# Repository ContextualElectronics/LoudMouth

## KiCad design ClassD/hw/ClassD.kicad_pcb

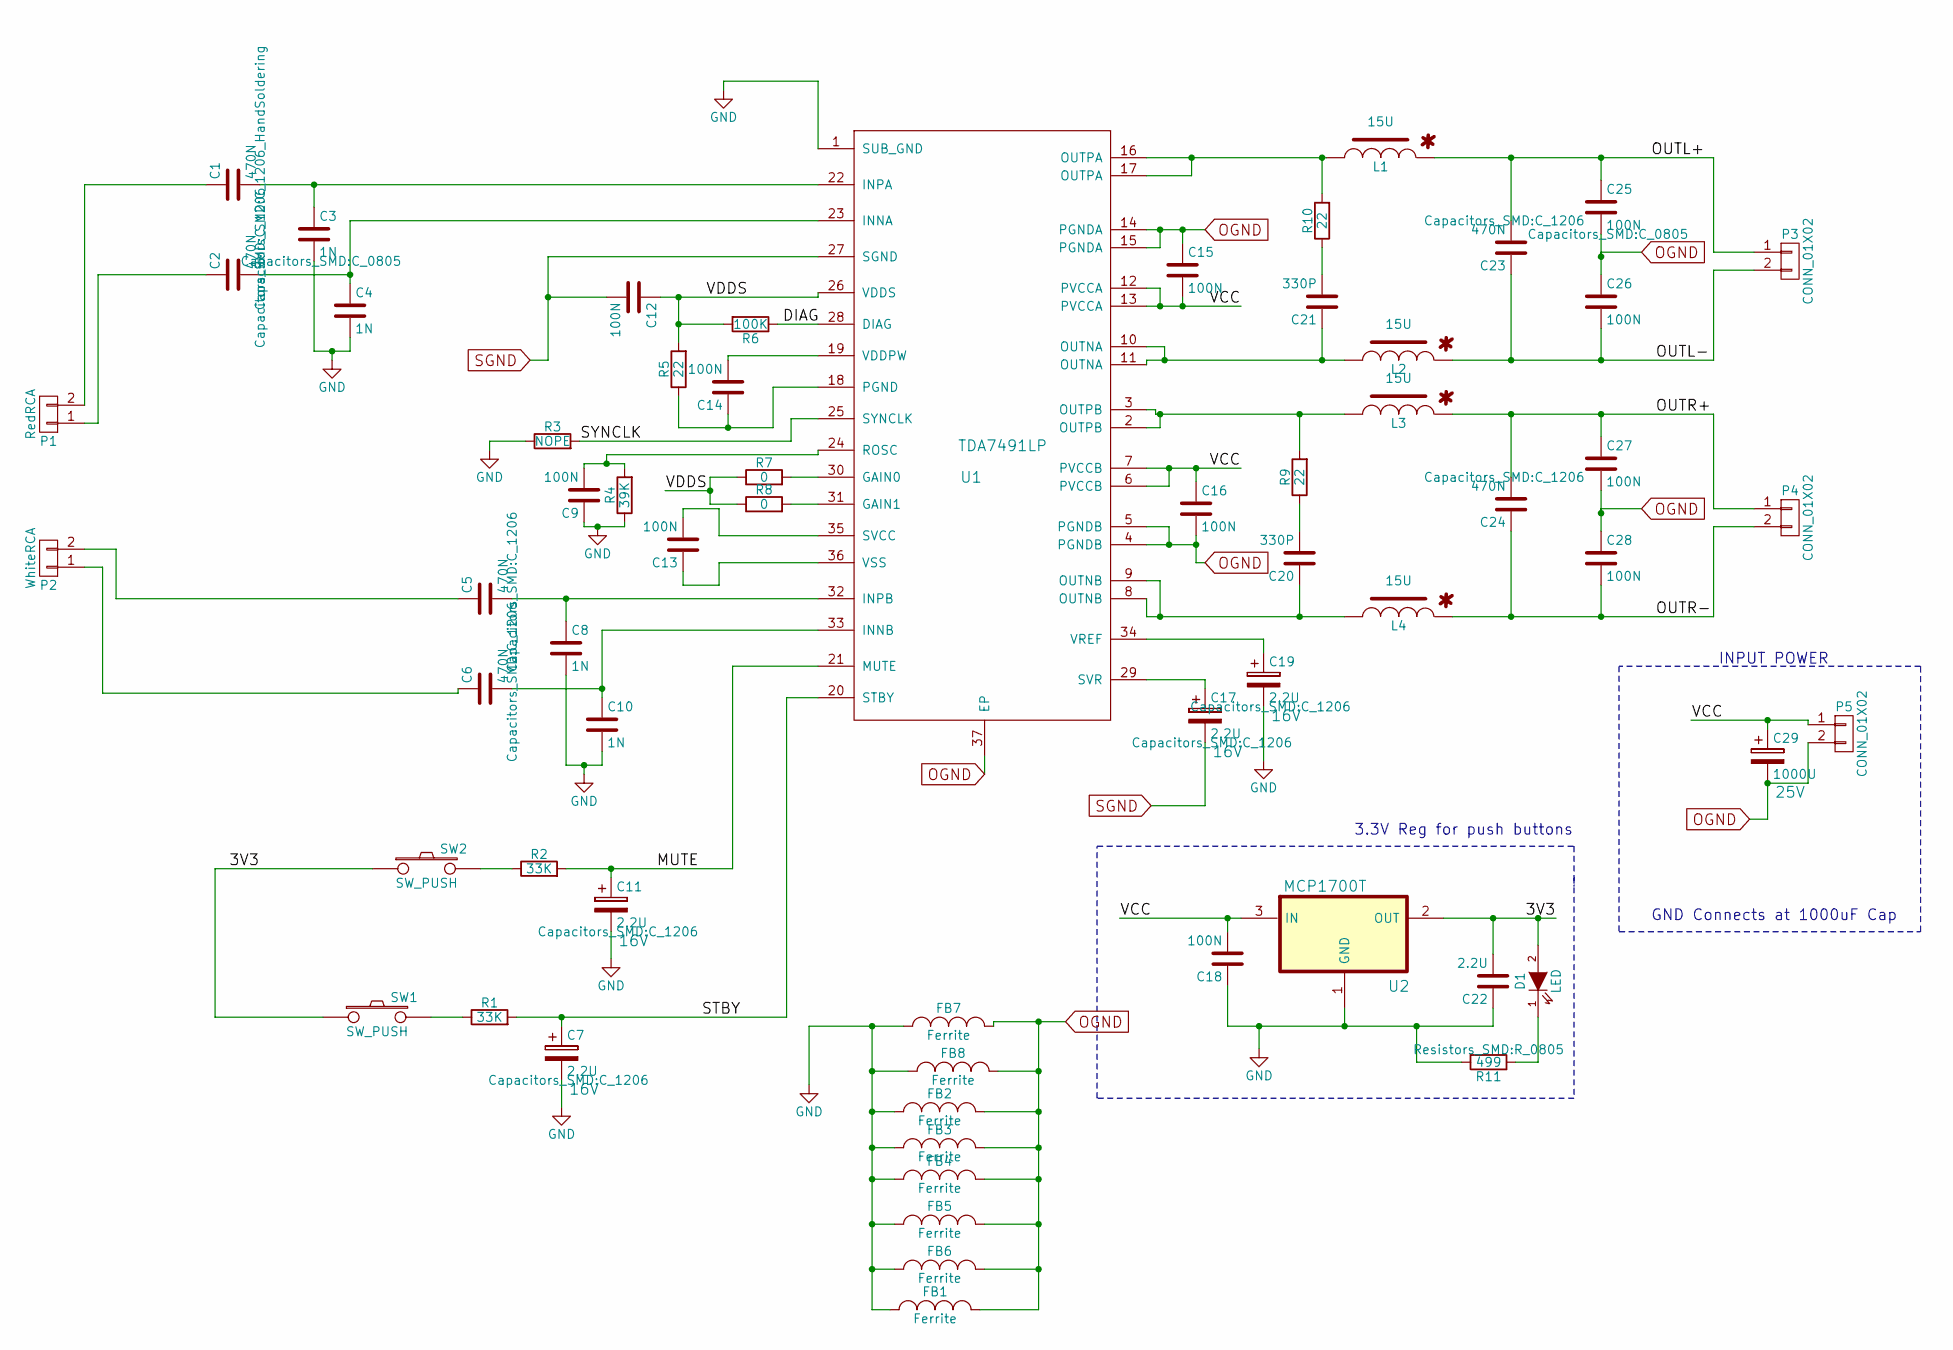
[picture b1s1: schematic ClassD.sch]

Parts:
C1: 470N; C_1206_HandSoldering; Voltage 25; MPN CL31B474KAFNNNE
C2, C5, C6, C23, C24: 470N; C_1206; Voltage 25; MPN CL31B474KAFNNNE
C3: 1N; C_0805; MPN C0805C102K5RACTU
C4, C8, C10: 1N; C_0805
C7, C11, C17, C19: 2.2U; C_1206; Voltage 16V; MPN C3216X7R1E225K160AA
C9, C12, C13, C14, C15, C16, C18, C26, C27, C28: 100N; C_0805
C20, C21: 330P; C_0805; MPN 0805YC334KAT2A
C22: 2.2U; C_1206
C25: 100N; C_0805; Voltage 16; MPN C0805C104K4RACTU
C29: 1000U; c_elec_13.6x13.6; Voltage 25V; MPN UUG1E102MNQ1MS
D1: LED; LED_0805
FB1, FB2, FB3, FB4, FB5, FB6, FB7, FB8: Ferrite; R_0805
L1, L2, L3, L4: 15U; NRS6045T150MMGK; MPN NRS6045T150MMGK
P1: RedRCA; RCJ1x; MPN RCJ-012
P2: WhiteRCA; RCJ1x; MPN RCJ013
P3, P4, P5: CONN_01X02; Pin_Header_Straight_1x02
R1, R2: 33K; R_0805
R3: NOPE; R_0805
R4: 39K; R_0805
R5, R9, R10: 22; R_0805
R6: 100K; R_0805
R7, R8: 0; R_0805
R11: 499; R_0805
SW1, SW2: SW_PUSH; FSM2JSMAA-ND; MPN FSM2JSMAA
U1: TDA7491LP; PowerSSO36-EPD; MPN TDA7491LP13TR
U2: MCP1700T; SOT-23; Voltage 3.3; MPN MCP1700T-3302E/TT

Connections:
/3V3: C22.2, D1.2 (A), SW1.1, SW2.1, U2.2 (OUT)
/DIAG: R6.1, U1.28 (DIAG)
/MUTE: C11.1, R2.2, U1.21 (MUTE)
/OUTL+: C23.2, C25.1, L1.1, P3.1
/OUTL-: C23.1, C26.2, L2.1, P3.2
/OUTR+: C24.2, C27.1, L3.1, P4.1
/OUTR-: C24.1, C28.2, L4.1, P4.2
/STBY: C7.1, R1.2, U1.20 (STBY)
/SYNCLK: R3.2, U1.25 (SYNCLK)
/VCC: C15.2, C16.1, C18.2, C29.1, P5.1, U1.6 (PVCCB), U1.7 (PVCCB), U1.12 (PVCCA), U1.13 (PVCCA), U2.3 (IN)
/VDDS: C12.1, R5.2, R6.2, R7.1, R8.1, U1.26 (VDDS)
GND: C3.2, C4.2, C7.2, C8.2, C9.1, C10.2, C11.2, C18.1, C19.2, C22.1, FB1.1, FB2.1, FB3.1, FB4.1, FB5.1, FB6.1, FB7.1, FB8.1, R3.1, R4.1, R11.2, U1.1 (SUB_GND), U2.1 (GND)
unnamed: C1.1, P1.2
unnamed: C1.2, C3.1, U1.22 (INPA)
unnamed: C2.1, P1.1
unnamed: C2.2, C4.1, U1.23 (INNA)
unnamed: C5.1, P2.2
unnamed: C5.2, C8.1, U1.32 (INPB)
unnamed: C6.1, P2.1
unnamed: C9.2, R4.2, U1.24 (ROSC)
unnamed: C6.2, C10.1, U1.33 (INNB)
unnamed: C13.1, U1.36 (VSS)
unnamed: C13.2, U1.35 (SVCC)
unnamed: C14.1, R5.1, U1.18 (PGND)
unnamed: C14.2, U1.19 (VDDPW)
unnamed: C17.1, U1.29 (SVR)
unnamed: C19.1, U1.34 (VREF)
unnamed: C20.1, L4.2, U1.8 (OUTNB), U1.9 (OUTNB)
unnamed: C20.2, R9.1
unnamed: C21.1, L2.2, U1.10 (OUTNA), U1.11 (OUTNA)
unnamed: C21.2, R10.1
unnamed: D1.1 (K), R11.1
unnamed: L1.2, R10.2, U1.16 (OUTPA), U1.17 (OUTPA)
unnamed: L3.2, R9.2, U1.2 (OUTPB), U1.3 (OUTPB)
unnamed: R1.1, SW1.2
unnamed: R2.1, SW2.2
unnamed: R7.2, U1.30 (GAIN0)
unnamed: R8.2, U1.31 (GAIN1)
OGND: C15.1, C16.2, C25.2, C26.1, C27.2, C28.1, C29.2, FB1.2, FB2.2, FB3.2, FB4.2, FB5.2, FB6.2, FB7.2, FB8.2, P5.2, U1.4 (PGNDB), U1.5 (PGNDB), U1.14 (PGNDA), U1.15 (PGNDA), U1.37 (EP)
SGND: C12.2, C17.2, U1.27 (SGND)

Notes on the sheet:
GND Connects at 1000uF Cap
INPUT POWER
3.3V Reg for push buttons

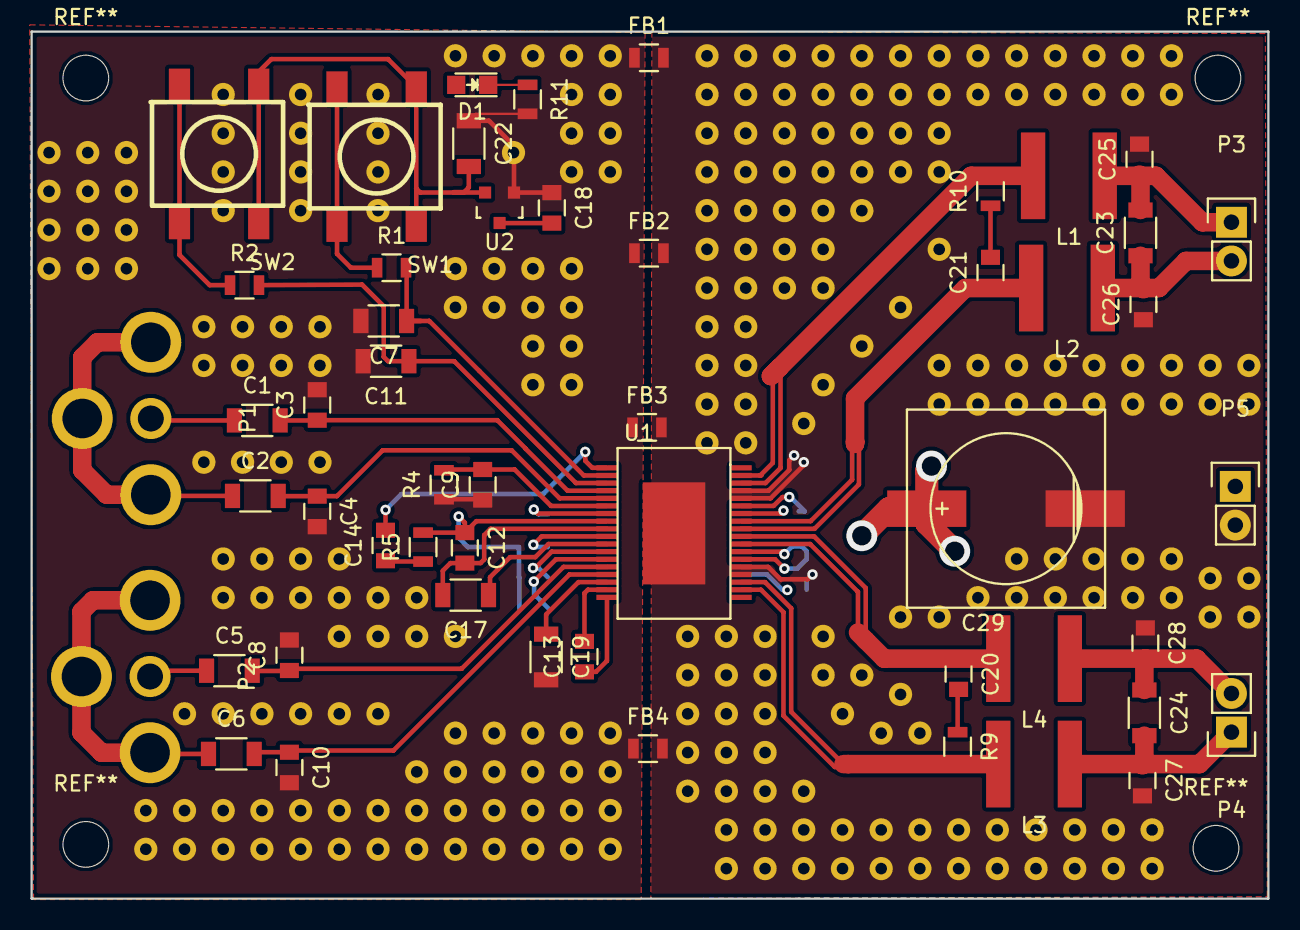
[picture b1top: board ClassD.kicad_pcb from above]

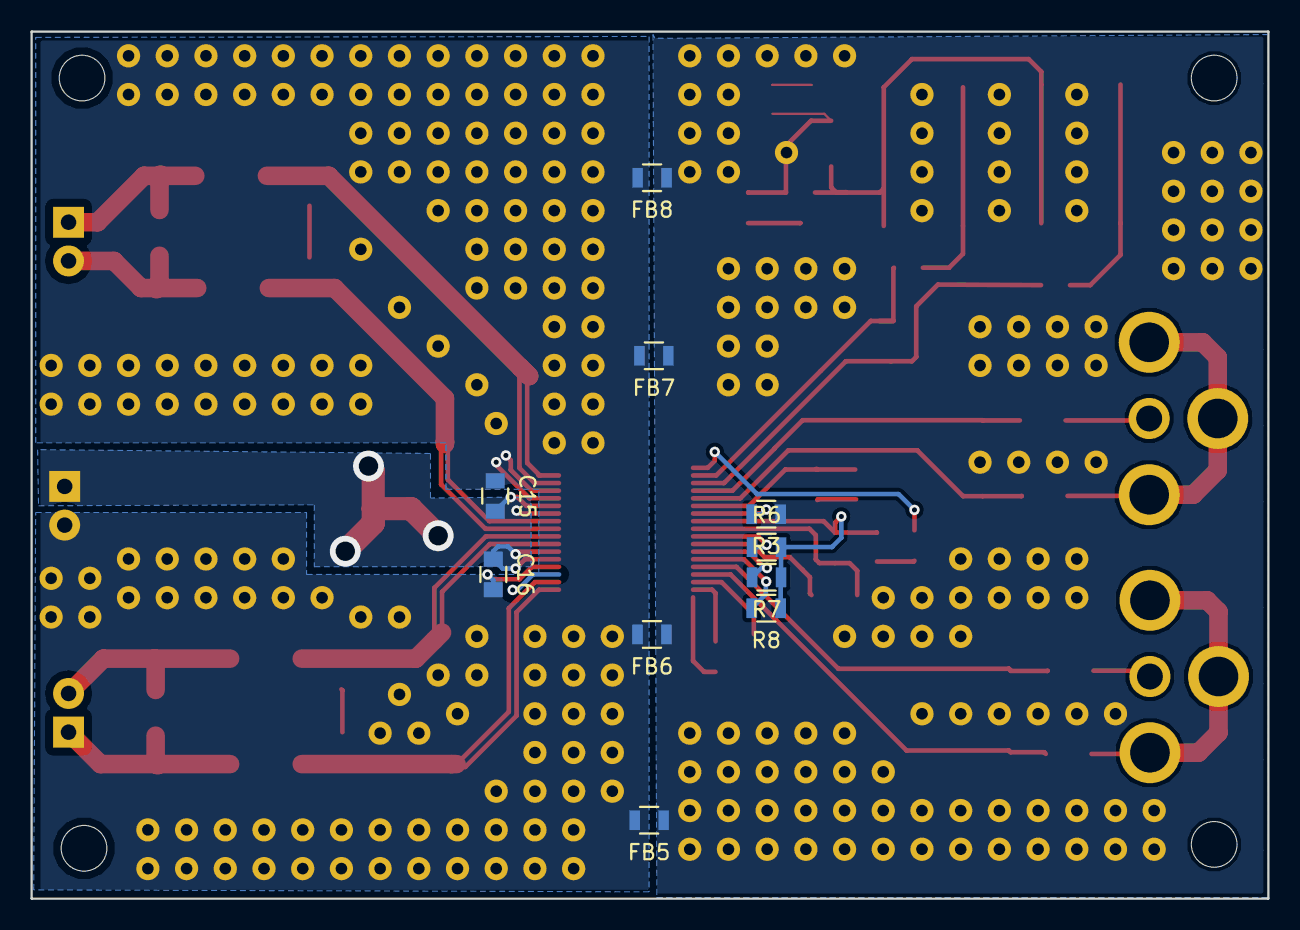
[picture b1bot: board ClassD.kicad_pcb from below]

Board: 2 copper layers, 81.2 x 56.9 mm, 62 parts (10 on the bottom side), 40 nets.

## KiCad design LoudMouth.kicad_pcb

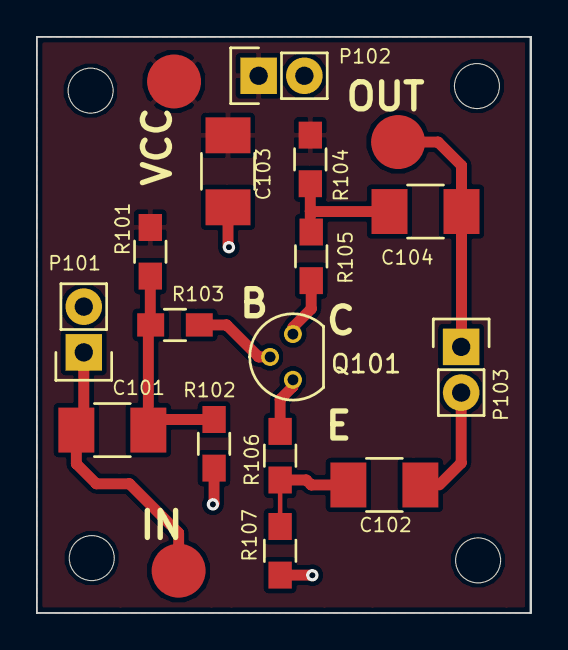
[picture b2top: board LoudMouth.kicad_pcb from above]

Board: 2 copper layers, 27.4 x 32.0 mm, 18 parts (0 on the bottom side), 10 nets.

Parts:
C101, C102, C103, C104: C; C_1210_HandSoldering
P101, P102, P103: CONN_01X02; Pin_Header_Straight_1x02
Q101: Q_NPN_EBC; TO-92_Molded_Narrow
R101, R102, R104, R107: R; R_0805_HandSoldering
R103, R105, R106: 0; R_0805_HandSoldering
TP101, TP102, TP103: CONN_01X01; Measurement_Point_Round-SMD-Pad_Big

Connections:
/BASE: Q101.2, R103.1
/COLLECTOR: Q101.3, R105.1
/EMITTER: Q101.1, R106.2
/IN: C101.2, P101.1, TP101.1
/OUT: C104.1, P103.1, TP103.1
/VCC: C103.2, P102.1, R101.1, R104.1, TP102.1
GND: C102.1, C103.1, P101.2, P102.2, P103.2, R102.2, R107.2
unnamed: C101.1, R101.2, R102.1, R103.2
unnamed: C102.2, R106.1, R107.1
unnamed: C104.2, R104.2, R105.2

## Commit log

2015-09-10 added schematic symbols
2015-09-10 Generated netlist and assigned footprints
2015-09-10 Created initial layout and changed input pin config
2015-09-10 Added all components to footprint
2015-09-10 Updated after DRC
2015-09-10 Finished Class A board, ready to send to fab
2015-10-05 Old gerber changes and new SPICE file for Class AB
2016-02-01 Move to separate directories for projects
2016-02-03 Started the Class D Schematic
2016-02-04 Created application schematic
2016-02-04 Updated schematic for ERC errors.
2016-02-07 Added critical component MPNs to the schematic
2016-02-11 Created and associated all footprints
2016-02-22 Updated footprint names in schematic
2016-02-22 Imported components and grouped geographically
2016-02-22 Added power indicator LED
2016-02-22 Added ferrites, finished component grouping
2016-03-16 Moved hardware files into a sub directory and added a document directory for pdfs
2016-03-16 Initial Layout Setup
2016-03-16 Placed RCA jacks, buttons and left side components
2016-03-16 Finished output filters (right side)
2016-03-17 Added planes and via stitching
2016-03-23 Finished layout with DRC
2016-03-24 Add 2nd capacitor
